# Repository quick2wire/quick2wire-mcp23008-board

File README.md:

# MCP23008 8 bit port expander board

This board uses the MCP23008 to add an 8-bit I/O port that is accessed using the I2C bus.

The board has been created but one has not yet been produced using these files.

-------------------------------------------------------
Copyright (c) 2013 Quick2Wire Ltd. http://quick2wire.com

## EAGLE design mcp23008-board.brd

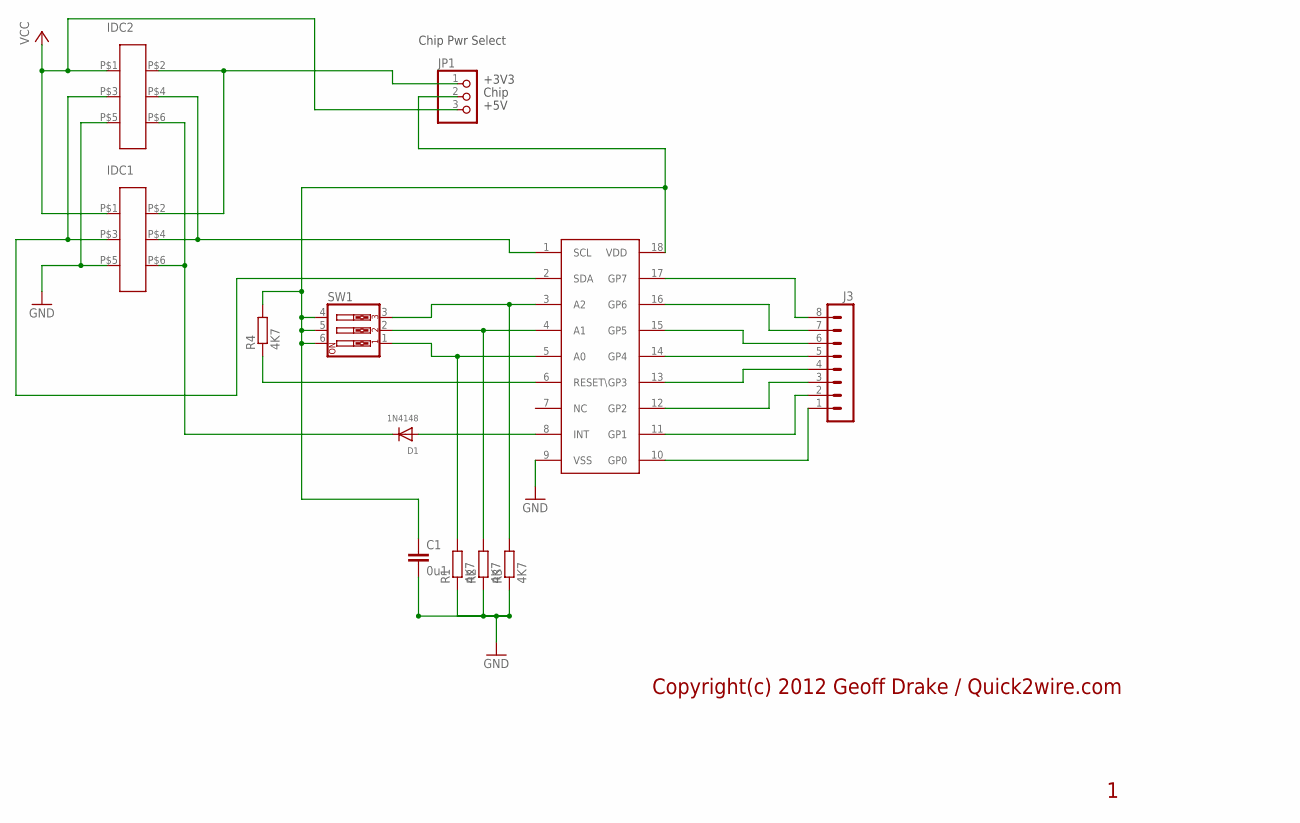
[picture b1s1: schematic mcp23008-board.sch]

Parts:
C1: 0u1; C025-030X050
D1: 1N4148; DO-1N4148
IC1: MCP23008; DIL18
IDC1, IDC2: IDC-6W
J3: MA08-1
JP1: PINHD-1X3; 1X03
R1, R2, R3, R4: 4K7; 0207/10
SW1: SW_DIP-3; EDG-03

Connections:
A0: IC1.5 (A0), R1.2, SW1.1
A1: IC1.4 (A1), R2.2, SW1.2
A2: IC1.3 (A2), R3.2, SW1.3
GND: C1.2, IC1.9 (VSS), IDC1.P$5, IDC2.P$5, R1.1, R2.1, R3.1
GP0: IC1.10 (GP0), J3.1
GP1: IC1.11 (GP1), J3.2
GP2: IC1.12 (GP2), J3.3
GP3: IC1.13 (GP3), J3.4
GP4: IC1.14 (GP4), J3.5
GP5: IC1.15 (GP5), J3.6
GP6: IC1.16 (GP6), J3.7
GP7: IC1.17 (GP7), J3.8
INT: D1.A, IC1.8 (INT)
unnamed: IC1.2 (SDA), IDC1.P$3, IDC2.P$3
unnamed: IC1.1 (SCL), IDC1.P$4, IDC2.P$4
unnamed: D1.C, IDC1.P$6, IDC2.P$6
unnamed: IDC1.P$2, IDC2.P$2, JP1.1
unnamed: C1.1, IC1.18 (VDD), JP1.2, R4.2, SW1.4, SW1.5, SW1.6
unnamed: IC1.6 (RESET\), R4.1
VCC: IDC1.P$1, IDC2.P$1, JP1.3

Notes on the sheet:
Copyright(c) 2012 Geoff Drake / Quick2wire.com
Chip Pwr Select
+5V
+3V3
Chip

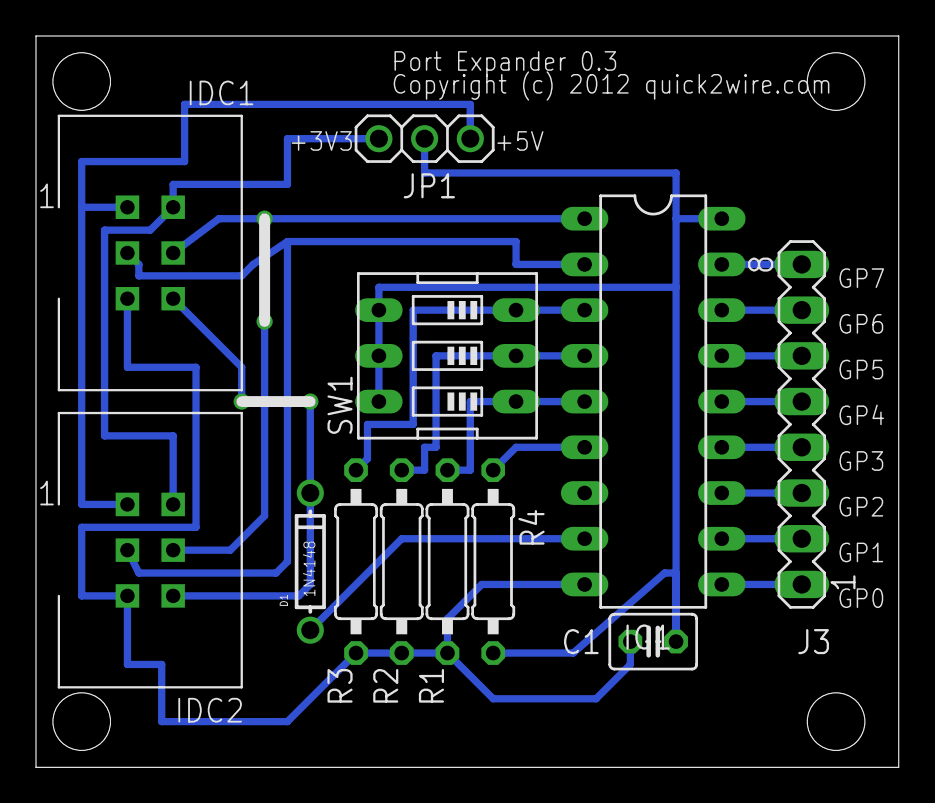
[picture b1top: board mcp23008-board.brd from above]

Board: 2 copper layers, 47.9 x 40.6 mm, 12 parts (0 on the bottom side), 20 nets.

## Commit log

2013-01-02 publishing version 0.2
2013-01-03 publishing version 0.3

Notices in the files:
mcp23008-board.brd:
Copyright (c) 2012 quick2wire.com
